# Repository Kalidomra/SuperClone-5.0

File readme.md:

# **SuperClone 5.0**

.jpg)

This is a clone of the Super Snapshot v5 hardware. All of the traces are close to the original and it will fit in the same case as an original. It uses an Atmel ATF16V8B in the place of the original PAL. I have also tried a ATF16V8C, but it did not work. All of the parts, including the Atmel are interchangeable with an original. I have also included the WinCUPL source files and a DigiKey bill of materials. The EEPROM is not available at DigiKey. I bought one from Ebay. 

The following parts will need to programmed:

  ATF16V8B-15PU --> This needs to be programmed with the include .jed file. 

  W27C512-45Z --> Programmed with any available Super Snapshot v5 ROM. See: https://rr.pokefinder.org/wiki/Super_Snapshot

It will also work with a larger 32 pin EEPROM like the W27C010-70 or W27C020-70. This is only required for a larger rom file like the SnappyROM:
https://github.com/adrianglz64/snappyrom

The EPROM used must be relatively fast (70ns or faster seems to work fine.) Some of the cheap, clone, UV erasable 27C512 EPROMS I tried did not work. I suspect they were remarked and in reality a slower part.

I have also included a 3d printable case. However, Hackup has made great case available here: https://www.thingiverse.com/thing:4623905

The original PCB was setup for 8K Ram, the clone is also defaulted this way. In order to use the 32K ram you need to cut the trace betrween pin 1 and 2 on J1 and then jumper pin 2 and 3 on J1.

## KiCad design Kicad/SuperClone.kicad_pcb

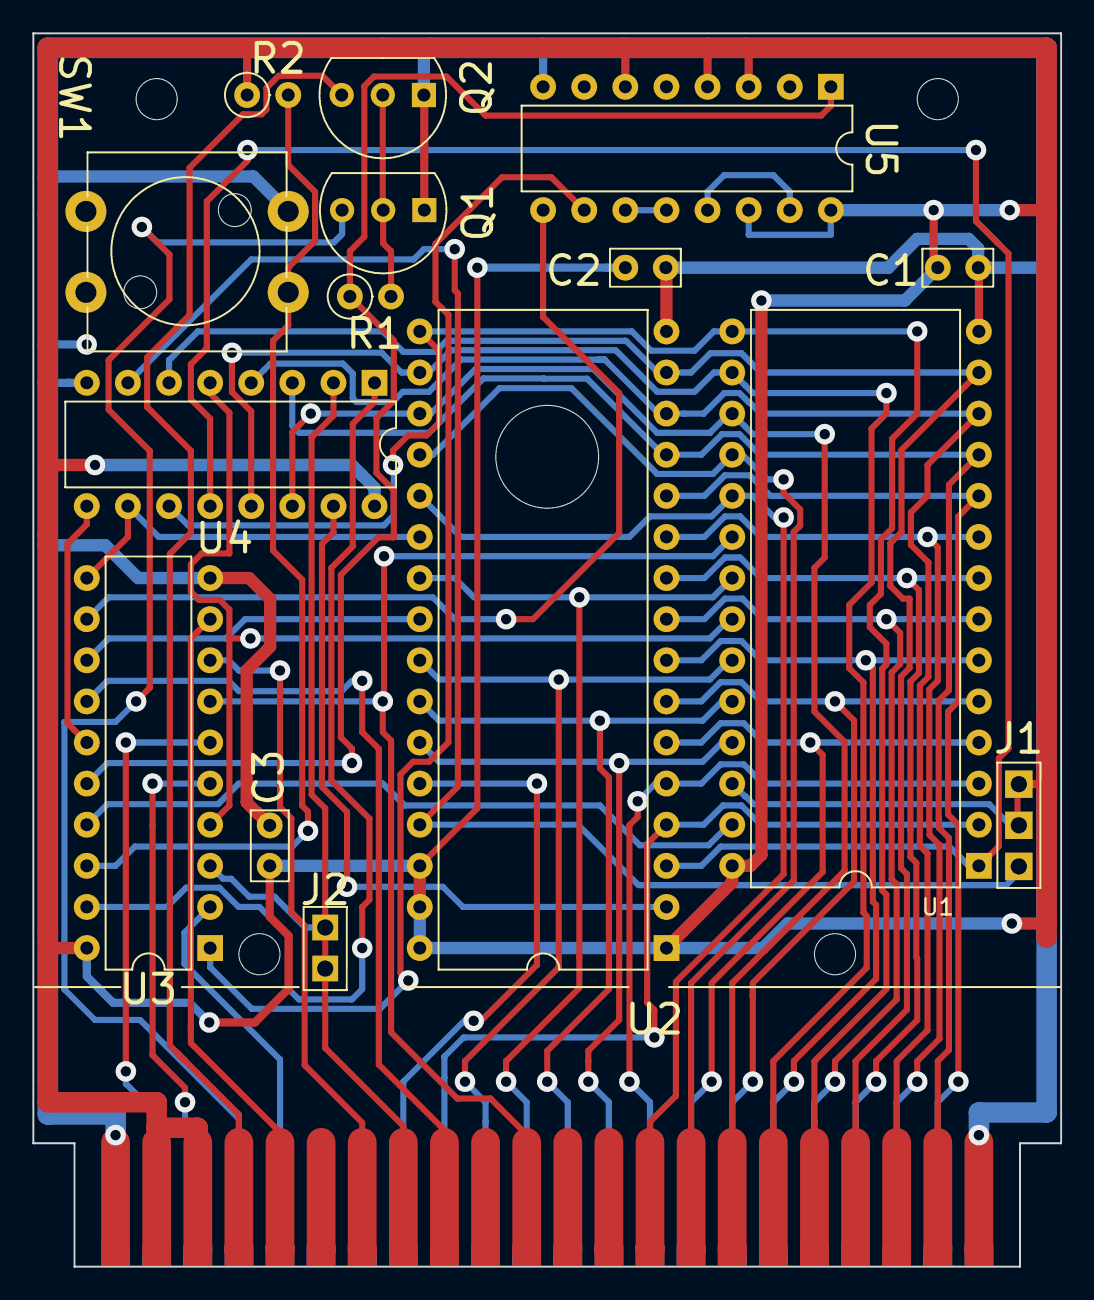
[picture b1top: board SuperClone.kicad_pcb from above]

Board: 2 copper layers, 63.5 x 76.2 mm, 16 parts (0 on the bottom side), 50 nets.

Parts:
C1, C2, C3: 100nF; C_Disc_D3.4mm_W2.1mm_P2.50mm
EXP1: EXPANSION_PORT-SuperClone; expansion_port
J1: Jumper_3_Bridged12; PinHeader_1x03_P2.54mm_Vertical
J2: Jumper_2_Bridged; PinHeader_1x02_P2.54mm_Vertical
Q1, Q2: PN2222A; TO-92L_Inline_Wide
R1, R2: 1.5K; R_Axial_DIN0207_L6.3mm_D2.5mm_P2.54mm_Vertical
SW1: SW_DIP_x01; SW_PUSH-12mm
U1: HM62256; DIP-28_W15.24mm_Socket
U2: 27C010; DIP-32_W15.24mm_Socket
U3: PAL16L8; DIP-20_W7.62mm_Socket
U4, U5: 74LS174; DIP-16_W7.62mm_Socket

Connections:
+5V: C1.1, C2.1, C3.1, EXP1.2, EXP1.3, J1.1, J1.2, R2.1, U1.26, U1.28, U2.1, U2.30, U2.31, U2.32, U3.20, U4.16, U5.3, U5.4, U5.6, U5.14, U5.16
/A0: EXP1.Y, U1.10, U2.12
/A1: EXP1.X, U1.9, U2.11
/A2: EXP1.W, U1.8, U2.10
/A3: EXP1.V, U1.7, U2.9
/A4: EXP1.U, U1.6, U2.8
/A5: EXP1.T, U1.5, U2.7
/A6: EXP1.S, U1.4, U2.6
/A7: EXP1.R, U1.3, U2.5
/A8: EXP1.P, U1.25, U2.27
/A9: EXP1.N, U1.24, U2.26
/A10: EXP1.M, U1.21, U2.23
/A11: EXP1.L, U1.23, U2.25
/A12: EXP1.K, U1.2, U2.4
/A13: EXP1.J, U2.28
/BA14: J1.3, U2.29, U4.7
/BA15: U1.1, U2.3, U4.12
/BA16: U2.2, U4.15
/CLKa: U3.12, U5.9
/CLKb: U3.15, U4.9
/CLRa: R1.1, U3.16, U5.1
/CLRb: U3.19, U4.1
/D0: EXP1.21, U1.11, U2.13, U4.3
/D1: EXP1.20, U1.12, U2.14, U4.4
/D2: EXP1.19, U1.13, U2.15, U4.6
/D3: EXP1.18, U1.15, U2.17, U4.11
/D4: EXP1.17, U1.16, U2.18, U4.13
/D5: EXP1.16, U1.17, U2.19, U4.14
/D6: EXP1.15, U1.18, U2.20
/D7: EXP1.14, U1.19, U2.21
/Delay: U3.1, U5.10
/Exrom: EXP1.9, U3.14
/Game: EXP1.8, J2.1, J2.2, U3.3, U4.2
/IOe: EXP1.7, U3.8
/IRQ: EXP1.4, Q2.3
/NMI: EXP1.D, Q1.3
/Phi2: EXP1.E, U3.2
/RW: EXP1.5, U3.9
/RamE: U1.22, U3.4, U4.5
/RamW: U1.27, U3.17
/Reset: EXP1.C, U3.5
/RomE: U2.22, U3.11, U4.10
/RomH: EXP1.B, U3.6
/RomL: EXP1.11, U1.20, U3.7
/RomOE: U2.24, U3.13
/key: R2.2, SW1.1, U3.18
GND: C1.2, C2.2, C3.2, EXP1.1, EXP1.22, EXP1.A, EXP1.Z, Q1.1, Q2.1, SW1.2, U1.14, U2.16, U3.10, U4.8, U5.8
unnamed: Q1.2, Q2.2, R1.2
unnamed: U5.11, U5.12
unnamed: U5.13, U5.15

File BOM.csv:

Part,Part Number,Description,Digikey
U1,HM6264 8k / HM62256 32k,"On HM6264 - Pin 26 is CS2 - Pull High
                         Pin 1 is Not Connected
On HM62256 - Pin 26 is A13
                           Pin 1 is A14
Need to modify J1 to use HM62256.",1450-1033-ND (32K) OR 1450-1036-ND (8K)
U2,27512 EPROM  (Used 32pin Socket),"Used 32 pin socket to enable future 128K upgrade
27C512 (64k) or 27C010 (128k) - W27C512-45Z (Ebay)",
U3,16L8 PAL,Use  ATF16V8B-15PU as substitute.,ATF16V8B-15PU-ND
U4,74LS174,,296-3664-5-ND
U5,74LS174,,296-3664-5-ND
Q1,PN2222A,,PN2222ATACT-ND
Q2,PN2222A,,PN2222ATACT-ND
R1,1.5K 1/4W,,CF14JT1K50CT-ND
R2,1.5K 1/4W,,CF14JT1K50CT-ND
C1,100nF,,1109PHCT-ND
C2,100nF,,1109PHCT-ND
C3,100nF,,1109PHCT-ND
SW1,ADTS24NV,,679-2374-ND
CAP,AKTSC22K,Switch Cap - 13mm dia vs 9.9mm for original,679-2315-ND
